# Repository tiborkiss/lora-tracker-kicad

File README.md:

# Träckthäspäck — a kid-friendly Meshtastic LoRa tracker

KiCad design of a small LoRa tracker board, created as a Swiss
[Zukunftstag](https://www.nationalerzukunftstag.ch/) project: with a group of children
we build a working Meshtastic tracker that the kids can take home and use.

The tracker is deliberately powered by **three ordinary AA batteries** — no
Li-ion cell — so it is simple and safe for children to handle and charge.

## Board

- Seeed Wio WM1110 module (LR1110 packet/radio controller)
- BMI270 motion sensor (wake-on-movement)
- ST7789 display on a 4-pin connector
- Active GNSS antenna + SMA LoRa antenna
- USB-C, SWD debug header
- Battery holder for 3× AA

## Firmware

The corresponding firmware is a Meshtastic fork and can be built from

<https://github.com/tiborkiss/firmware.git>, branch `bringup/wio-st7789-lcd`.

## Repository contents

- `träckthäspäck.kicad_sch` / `.kicad_pcb` / `.kicad_pro` — schematic and PCB
- `träckthäspäck.csv` — bill of materials
- `träcker 01.pdf` — board rendering
- `KiCAD-Shortcuts-PDF.pdf` — KiCad shortcut cheat sheet

## License

MIT — see [LICENSE](LICENSE).

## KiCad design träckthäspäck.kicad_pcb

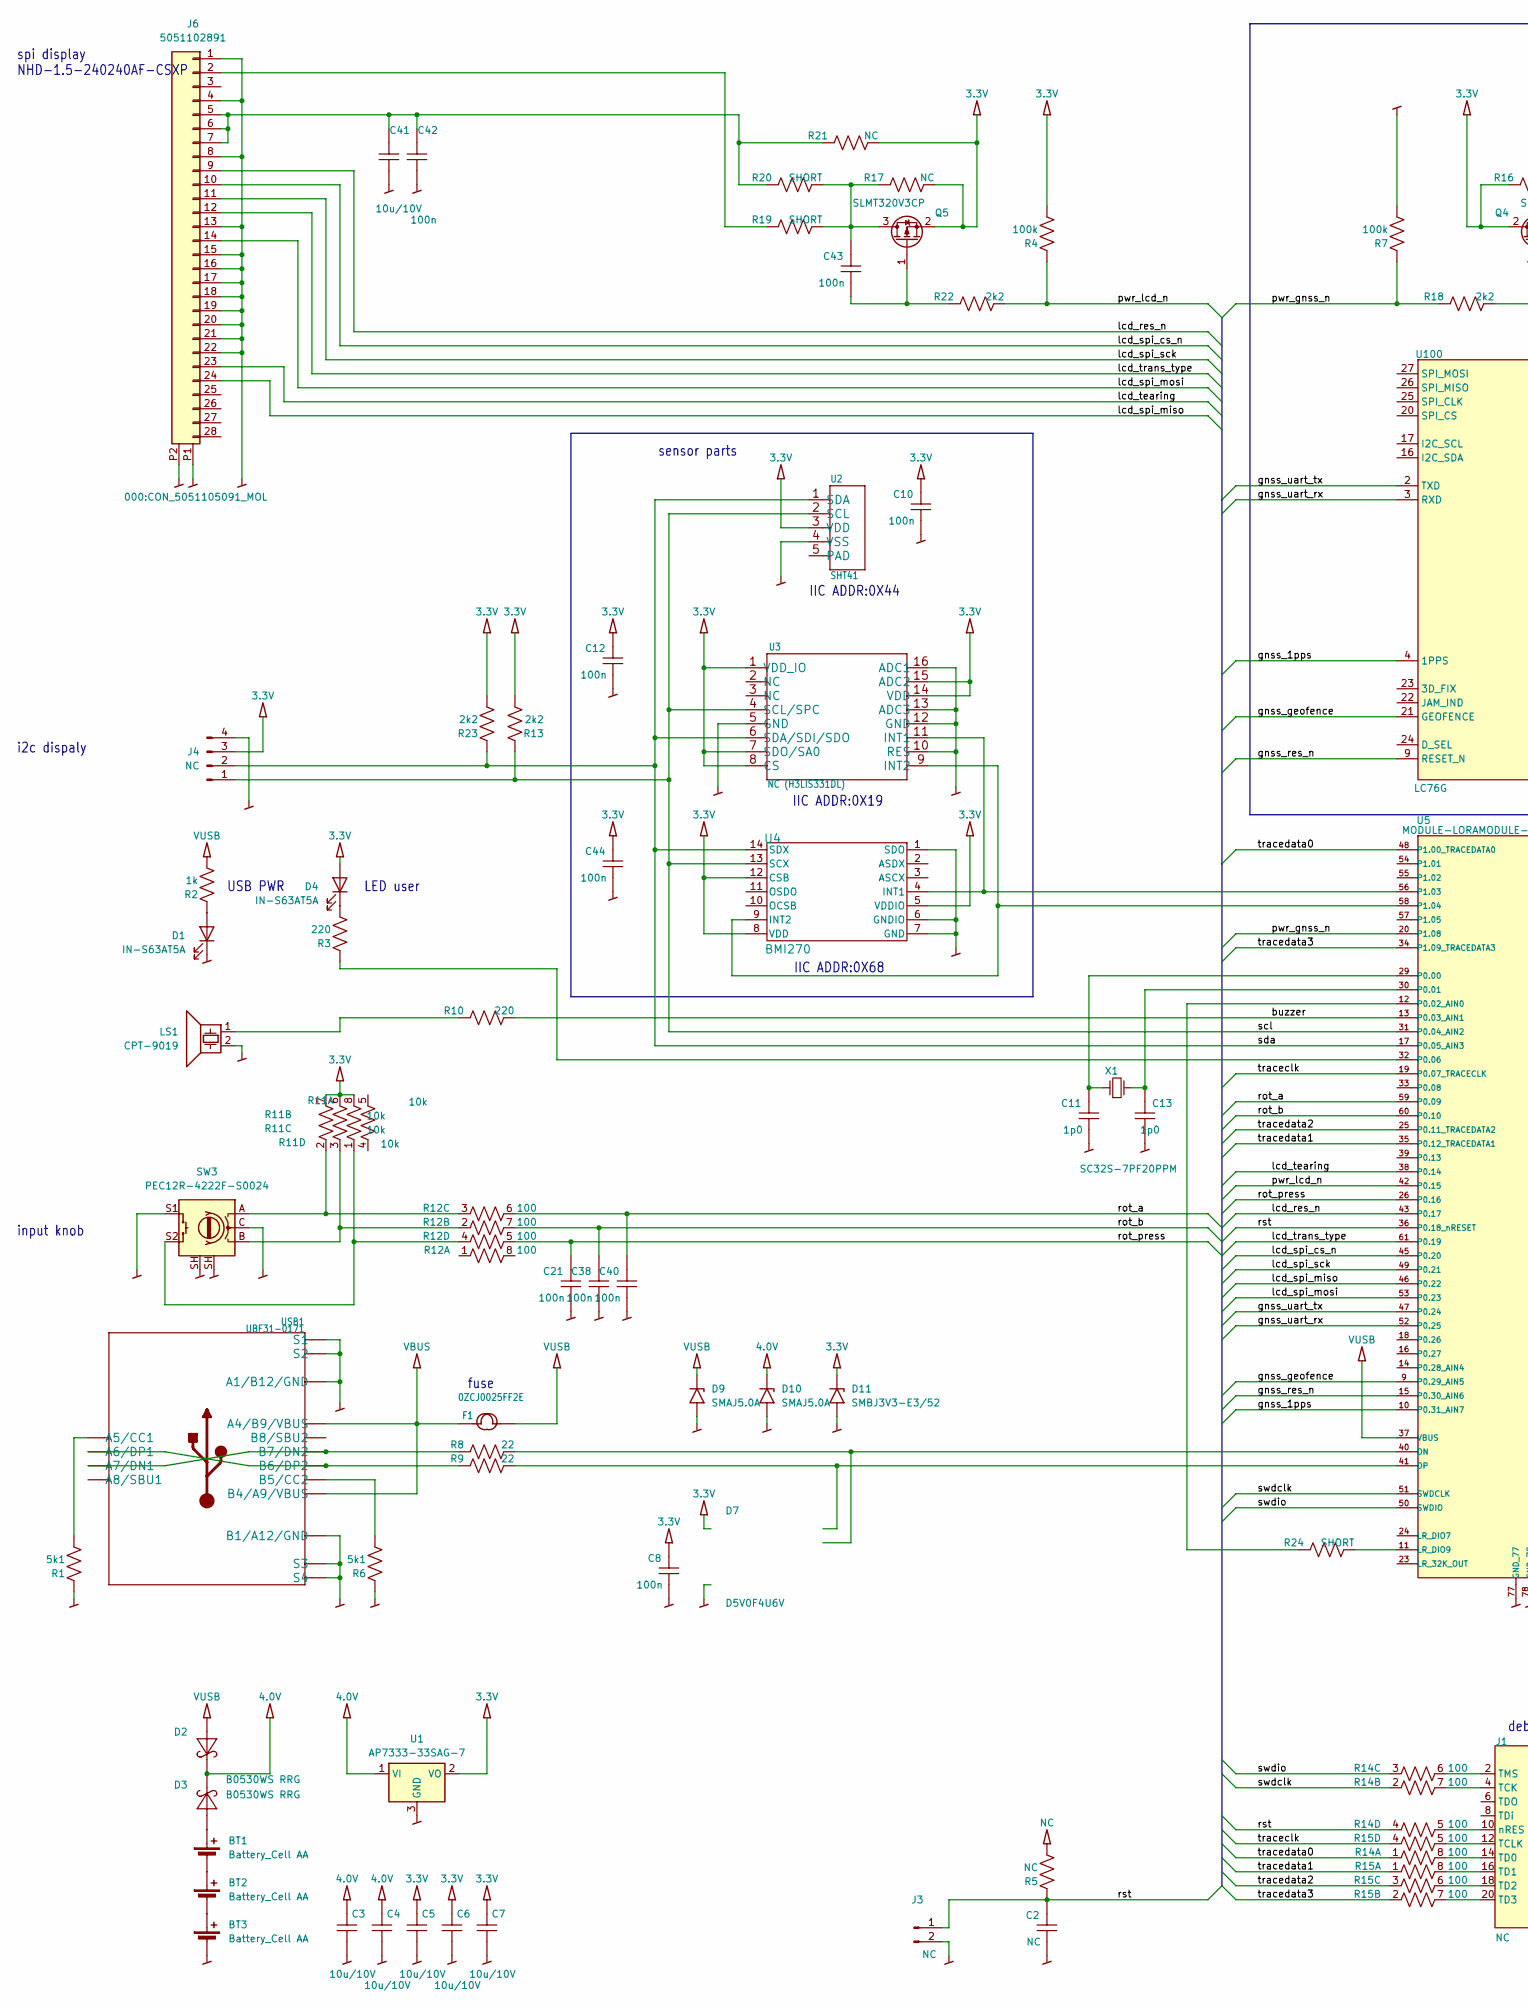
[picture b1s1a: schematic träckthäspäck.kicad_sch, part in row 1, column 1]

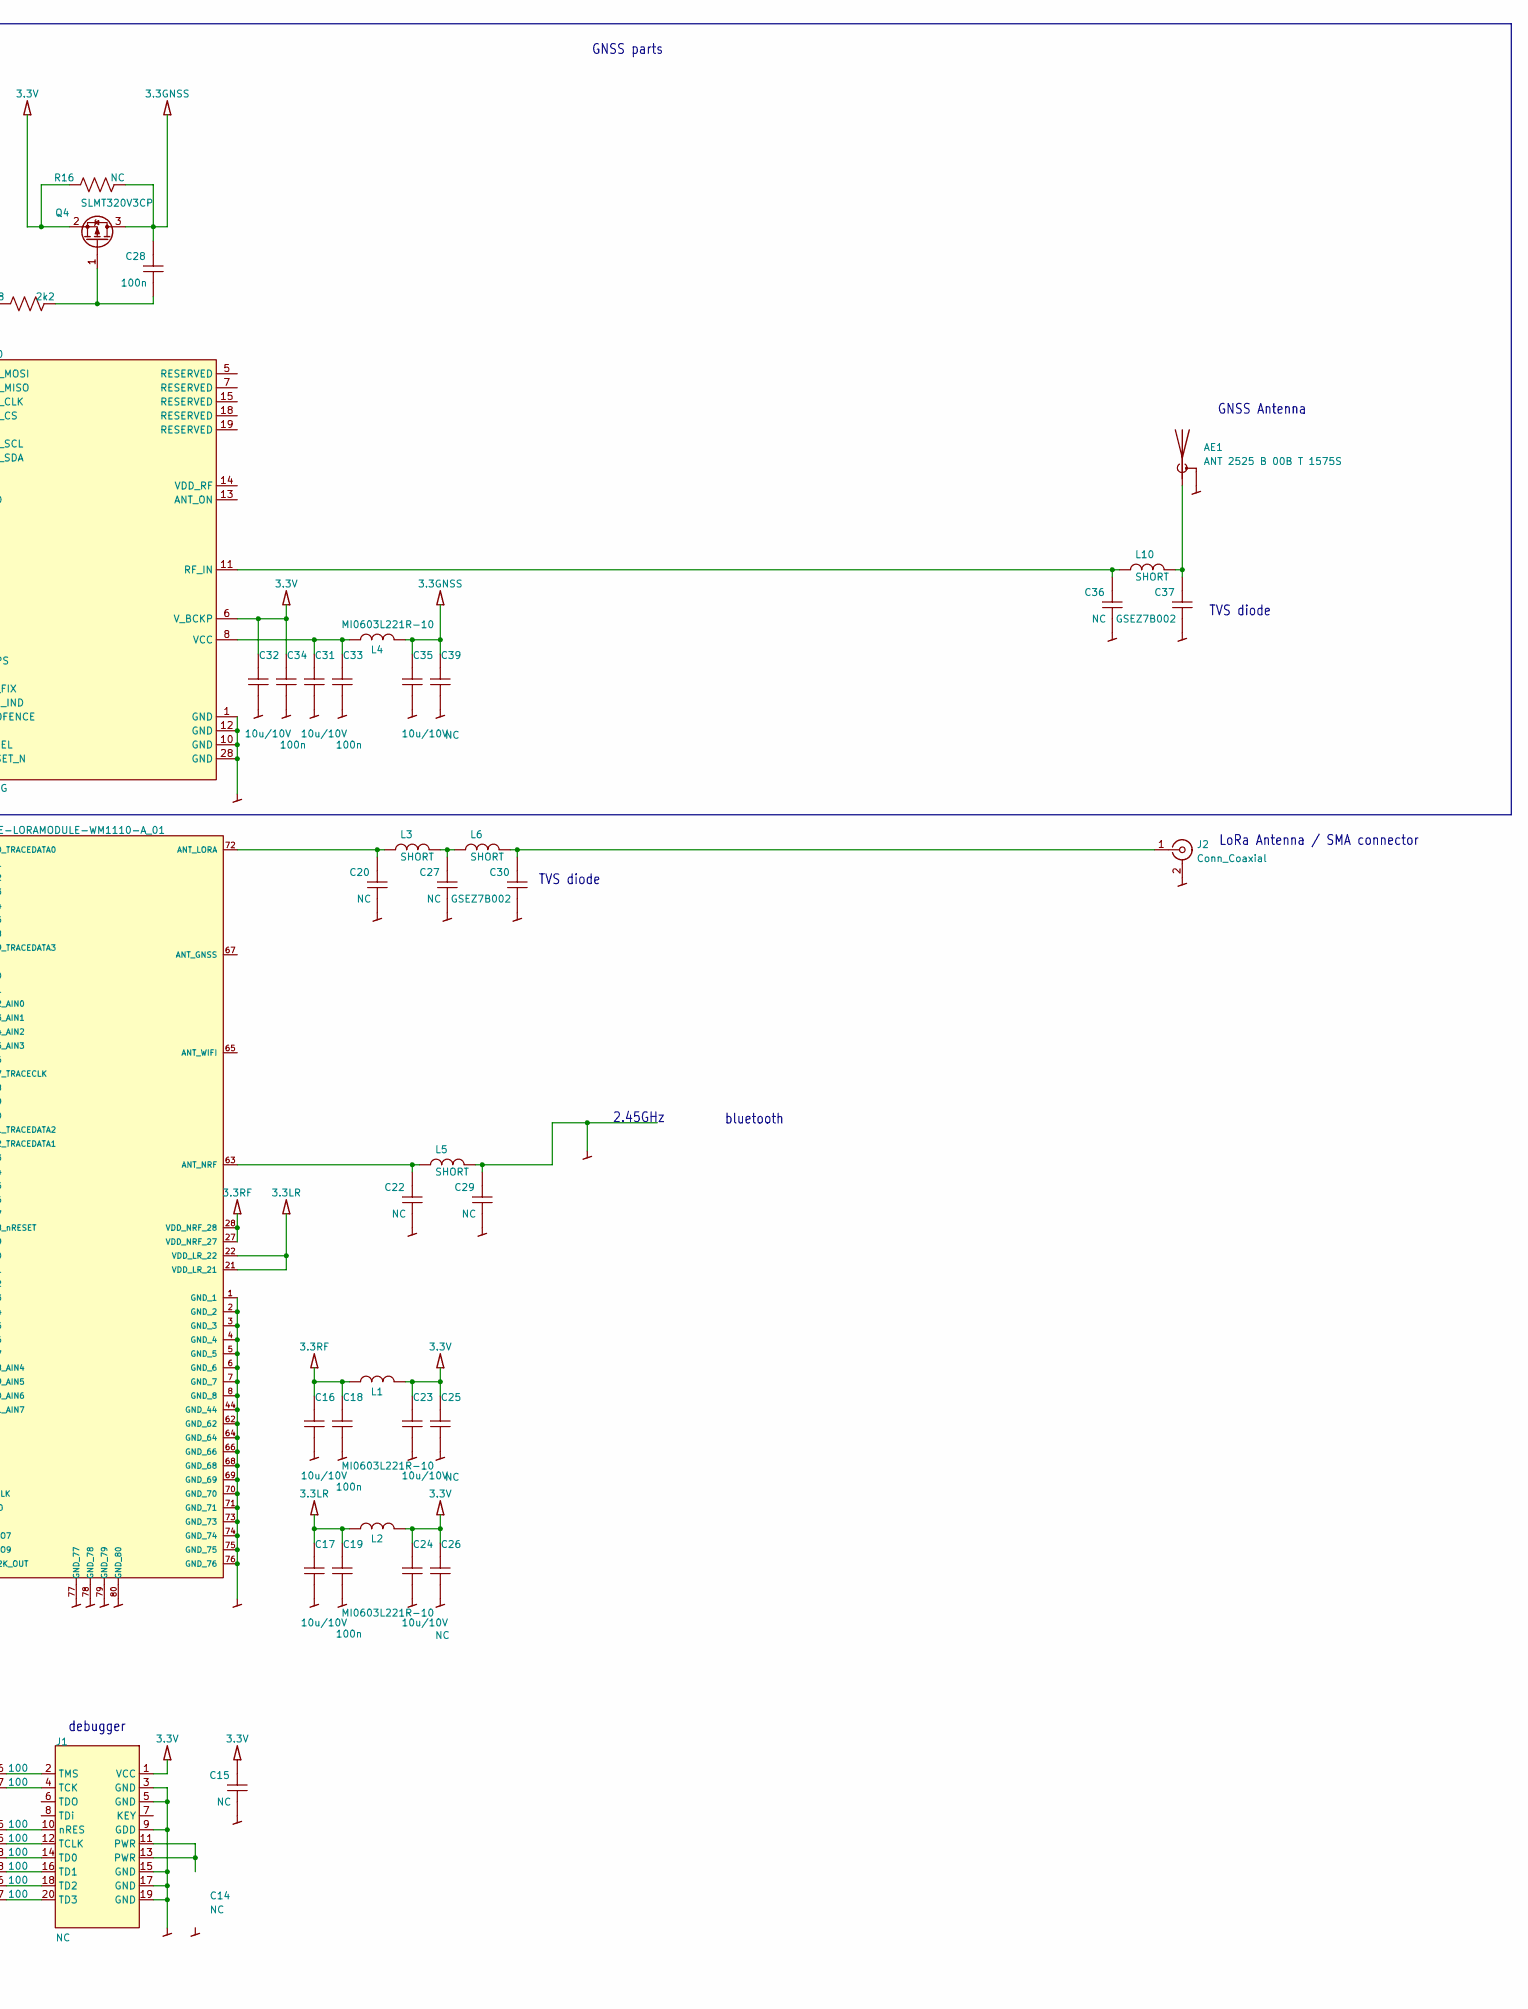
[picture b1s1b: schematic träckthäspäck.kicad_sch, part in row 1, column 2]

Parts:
AE1: ANT 2525 B 00B T 1575S
BT1, BT2, BT3: Battery_Cell AA; keystone_2460
C2, C14, C15, C20, C22, C25, C26, C27, C29, C36, C39: NC; 0402_C
C3, C4, C5, C6, C7, C16, C17, C23, C24, C31, C32, C35, C41: 10u/10V; 0603_C
C8, C10, C12, C18, C19, C21, C28, C33, C34, C38, C40, C42, C43, C44: 100n; 0402_C
C11, C13: 1p0; 0402_C
C30, C37: GSEZ7B002; 0402_C
D1, D4: IN-S63AT5A; LED_0603_1608Metric
D2, D3: B0530WS RRG; D_SOD-323F
D7: D5V0F4U6V; SOT-563
D9, D10: SMAJ5.0A; D_SMA
D11: SMBJ3V3-E3/52; D_SMA
F1: 0ZCJ0025FF2E; FS1206
J1: NC; PinHeader_2x10_P1.27mm_Vertical_SMD
J2: Conn_Coaxial; SMA_Amphenol_132134_Vertical
J3: NC; PinHeader_1x02_P2.00mm_Vertical
J4: NC; Molex_Micro-Latch_53253-0470_1x04_P2.00mm_Vertical
J6: 5051102891; CON_5051105091_MOL
L1, L2, L4: MI0603L221R-10; 0603_L
L3, L5, L6, L10: SHORT; 0402_L
LS1: CPT-9019; Buzzer_CUI_CPT-9019S-SMT
Q4, Q5: SLMT320V3CP; SOT-23
R1, R6: 5k1; 0402_R
R2: 1k; 0402_R
R3, R10: 220; 0402_R
R4, R7: 100k; 0402_R
R5, R16, R17, R21: NC; 0402_R
R8, R9: 22; 0402_R
R11: 10k; 0804-8
R12, R14, R15: 100; 0804-8
R13, R18, R22, R23: 2k2; 0402_R
R19, R20, R24: SHORT; 0402_R
SW3: PEC12R-4222F-S0024; RotaryEncoder_Bourns_Vertical_PEC12R-3x17F-S--oli
U1: AP7333-33SAG-7; SOT-23
U2: SHT41; SNR4-0.8-1.5X1.5X0.54MM
U3: NC (H3LIS331DL); LGA16-0.5-3X3MM
U4: BMI270; BMI270_BOS
U5: MODULE-LORAMODULE-WM1110-A_01; MODULE72_0D9_20X20X2MM
U100: LC76G
USB1: UBF31-0171; USB2.0-TYPE-C
X1: SC32S-7PF20PPM; XTAL2-1.5X3.2

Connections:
3.3GNSS: C28.1, C35.1, C39.1, L4.1, Q4.3 (D), R16.1
3.3LR: C17.1, C19.1, L2.2, U5.21 (VDD_LR_21), U5.22 (VDD_LR_22)
3.3RF: C16.1, C18.1, L1.2, U5.27 (VDD_NRF_27), U5.28 (VDD_NRF_28)
3.3V: C5.1, C6.1, C7.1, C8.1, C10.1, C12.1, C15.1, C23.1, C24.1, C25.1, C26.1, C32.1, C34.1, C44.1, D4.2 (A), D7.5 (VCC), D11.1 (A1), J1.1 (VCC), J4.3, L1.1, L2.1, Q4.2 (S), Q5.2 (S), R4.1, R11.6 (2), R11.7 (2), R11.8 (2), R13.1, R16.2, R17.1, R21.1, R23.1, U1.2 (VO), U2.3 (VDD), U3.1 (VDD_IO), U3.7 (SDO/SA0), U3.8 (CS), U3.14 (VDD), U3.15 (ADC2), U4.5 (VDDIO), U4.8 (VDD), U4.12 (CSB), U100.6 (V_BCKP)
4.0V: C3.1, C4.1, D2.1, D3.1, D10.1 (A1), U1.1 (VI)
/buzzer: R10.1, U5.13 (P0.03_AIN1)
/gnss_1pps: U5.10 (P0.31_AIN7), U100.4 (1PPS)
/gnss_geofence: U5.9 (P0.29_AIN5), U100.21 (GEOFENCE)
/gnss_res_n: U5.15 (P0.30_AIN6), U100.9 (RESET_N)
/gnss_uart_rx: U5.52 (P0.25), U100.3 (RXD)
/gnss_uart_tx: U5.47 (P0.24), U100.2 (TXD)
/lcd_res_n: J6.9, U5.43 (P0.17)
/lcd_spi_cs_n: J6.10, U5.45 (P0.20)
/lcd_spi_miso: J6.24, U5.46 (P0.22)
/lcd_spi_mosi: J6.14, U5.53 (P0.23)
/lcd_spi_sck: J6.11, U5.49 (P0.21)
/lcd_tearing: J6.23, U5.38 (P0.14)
/lcd_trans_type: J6.12, U5.61 (P0.19)
/pwr_gnss_n: R7.2, R18.2, U5.20 (P1.08)
/pwr_lcd_n: R4.2, R22.1, U5.42 (P0.15)
/rot_a: C40.1, R12.6 (2), U5.59 (P0.09)
/rot_b: C38.1, R12.7 (2), U5.60 (P0.10)
/rot_press: C21.1, R12.5 (2), U5.26 (P0.16)
/rst: C2.1, J3.1, R5.2, R14.4 (1), U5.36 (P0.18_nRESET)
/scl: J4.1, R13.2, U2.2 (SCL), U3.4 (SCL/SPC), U4.13 (SCX), U5.31 (P0.04_AIN2)
/sda: J4.2, R23.2, U2.1 (SDA), U3.6 (SDA/SDI/SDO), U4.14 (SDX), U5.17 (P0.05_AIN3)
/swdclk: R14.2 (1), U5.51 (SWDCLK)
/swdio: R14.3 (1), U5.50 (SWDIO)
/traceclk: R15.4 (1), U5.19 (P0.07_TRACECLK)
/tracedata0: R14.1, U5.48 (P1.00_TRACEDATA0)
/tracedata1: R15.1, U5.35 (P0.12_TRACEDATA1)
/tracedata2: R15.3 (1), U5.25 (P0.11_TRACEDATA2)
/tracedata3: R15.2 (1), U5.34 (P1.09_TRACEDATA3)
GND: AE1.2 (Shield), BT3.2 (-), C2.2, C3.2, C4.2, C5.2, C6.2, C7.2, C8.2, C10.2, C11.2, C12.2, C13.2, C14.2, C15.2, C16.2, C17.2, C18.2, C19.2, C20.2, C21.2, C22.2, C23.2, C24.2, C25.2, C26.2, C27.2, C29.2, C30.2, C31.2, C32.2, C33.2, C34.2, C35.2, C36.2, C37.2, C38.2, C39.2, C40.2, C41.2, C42.2, C44.2, D1.1 (K), D7.2 (GND), D9.2 (A2), D10.2 (A2), D11.2 (A2), J1.3 (GND), J1.5 (GND), J1.9 (GDD), J1.15 (GND), J1.17 (GND), J1.19 (GND), J2.2 (Ext), J3.2, J4.4, J6.1, J6.4, J6.8, J6.13, J6.15, J6.16, J6.17, J6.18, J6.19, J6.20, J6.21, J6.22, J6.P1, J6.P2, LS1.2, R1.2, R6.2, R7.1, SW3.C, SW3.S1, SW3.SH, U1.3 (GND), U2.4 (VSS), U3.5 (GND), U3.10 (RES), U3.12 (GND), U3.13 (ADC3), U3.16 (ADC1), U4.1 (SDO), U4.6 (GNDIO), U4.7 (GND), U5.1 (GND_1), U5.2 (GND_2), U5.3 (GND_3), U5.4 (GND_4), U5.5 (GND_5), U5.6 (GND_6), U5.7 (GND_7), U5.8 (GND_8), U5.44 (GND_44), U5.62 (GND_62), U5.64 (GND_64), U5.66 (GND_66), U5.68 (GND_68), U5.69 (GND_69), U5.70 (GND_70), U5.71 (GND_71), U5.73 (GND_73), U5.74 (GND_74), U5.75 (GND_75), U5.76 (GND_76), U5.77 (GND_77), U5.78 (GND_78), U5.79 (GND_79), U5.80 (GND_80), U100.1 (GND), U100.10 (GND), U100.12 (GND), U100.28 (GND), USB1.A1_B12 (A1/B12/GND), USB1.B1_A12 (B1/A12/GND), USB1.S1, USB1.S2, USB1.S3, USB1.S4, USB1.S5 (S1), USB1.S6 (S2)
GND_A2: C29.1, L5.1
NC: R5.1
unnamed: AE1.1 (A), C37.1, L10.1
unnamed: BT1.1 (+), D3.2
unnamed: BT1.2 (-), BT2.1 (+)
unnamed: BT2.2 (-), BT3.1 (+)
unnamed: C14.1, J1.11 (PWR), J1.13 (PWR)
unnamed: C27.1, L3.1, L6.2
unnamed: D1.2 (A), R2.2
unnamed: D4.1 (K), R3.1
unnamed: D7.1 (CH1), R9.1, U5.41 (DP)
unnamed: D7.3 (CH2), R8.1, U5.40 (DN)
unnamed: J1.4 (TCK), R14.7 (2)
unnamed: J1.12 (TCLK), R15.5 (2)
unnamed: J1.14 (TD0), R14.8 (2)
unnamed: J1.16 (TD1), R15.8 (2)
unnamed: J1.18 (TD2), R15.6 (2)
unnamed: J1.20 (TD3), R15.7 (2)
unnamed: J1.2 (TMS), R14.6 (2)
unnamed: J1.10 (nRES), R14.5 (2)
unnamed: C30.1, J2.1 (In), L6.1
unnamed: J6.2, R19.2
unnamed: C41.1, C42.1, J6.5, J6.6, J6.7, R20.2, R21.2
unnamed: LS1.1, R10.2
unnamed: C28.2, Q4.1 (G), R18.1
unnamed: C43.1, Q5.3 (D), R17.2, R19.1, R20.1
unnamed: C43.2, Q5.1 (G), R22.2
unnamed: R11.2 (1), R12.3 (1), SW3.A
unnamed: R11.3 (1), R12.2 (1), SW3.B
unnamed: R11.1, R12.4 (1), SW3.S2
unnamed: U3.11 (INT1), U4.4 (INT1), U5.56 (P1.03)
unnamed: U3.9 (INT2), U4.9 (INT2), U5.58 (P1.04)
unnamed: C20.1, L3.2, U5.72 (ANT_LORA)
unnamed: C22.1, L5.2, U5.63 (ANT_NRF)
unnamed: R24.1, U5.11 (LR_DIO9)
unnamed: C11.1, U5.29 (P0.00), X1.2
unnamed: C13.1, U5.30 (P0.01), X1.1
unnamed: R24.2, U5.12 (P0.02_AIN0)
unnamed: R3.2, U5.32 (P0.06)
unnamed: C36.1, L10.2, U100.11 (RF_IN)
unnamed: C31.1, C33.1, L4.2, U100.8 (VCC)
unnamed: R1.1, USB1.A5 (A5/CC1)
unnamed: R9.2, USB1.A6 (A6/DP1), USB1.B6 (B6/DP2)
unnamed: R8.2, USB1.A7 (A7/DN1), USB1.B7 (B7/DN2)
unnamed: R6.1, USB1.B5 (B5/CC2)
VBUS: F1.1, USB1.A4_B9 (A4/B9/VBUS), USB1.B4_A9 (B4/A9/VBUS)
VUSB: D2.2, D9.1 (A1), F1.2, R2.1, U5.37 (VBUS)

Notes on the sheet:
sensor parts
2.45GHz
TVS diode
GNSS Antenna
fuse
spi display NHD-1.5-240240AF-CSXP
LED user
IIC ADDR:0X44
IIC ADDR:0X68
USB PWR
bluetooth
IIC ADDR:0X19
LoRa Antenna / SMA connector
i2c dispaly
input knob
debugger
GNSS parts

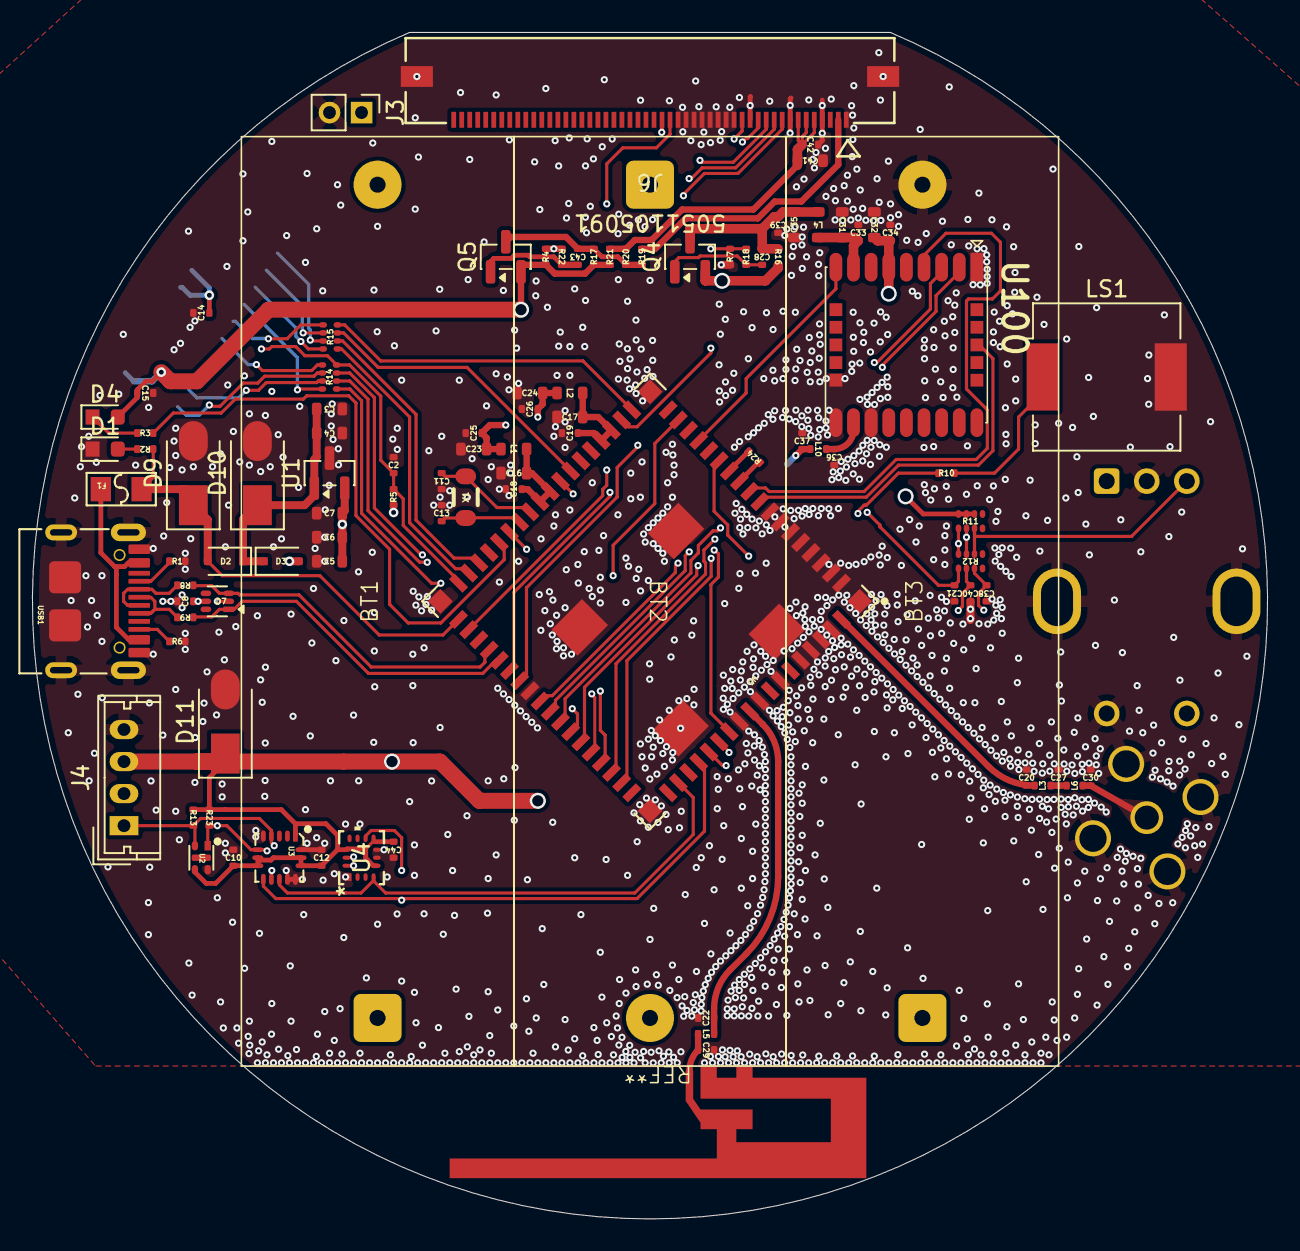
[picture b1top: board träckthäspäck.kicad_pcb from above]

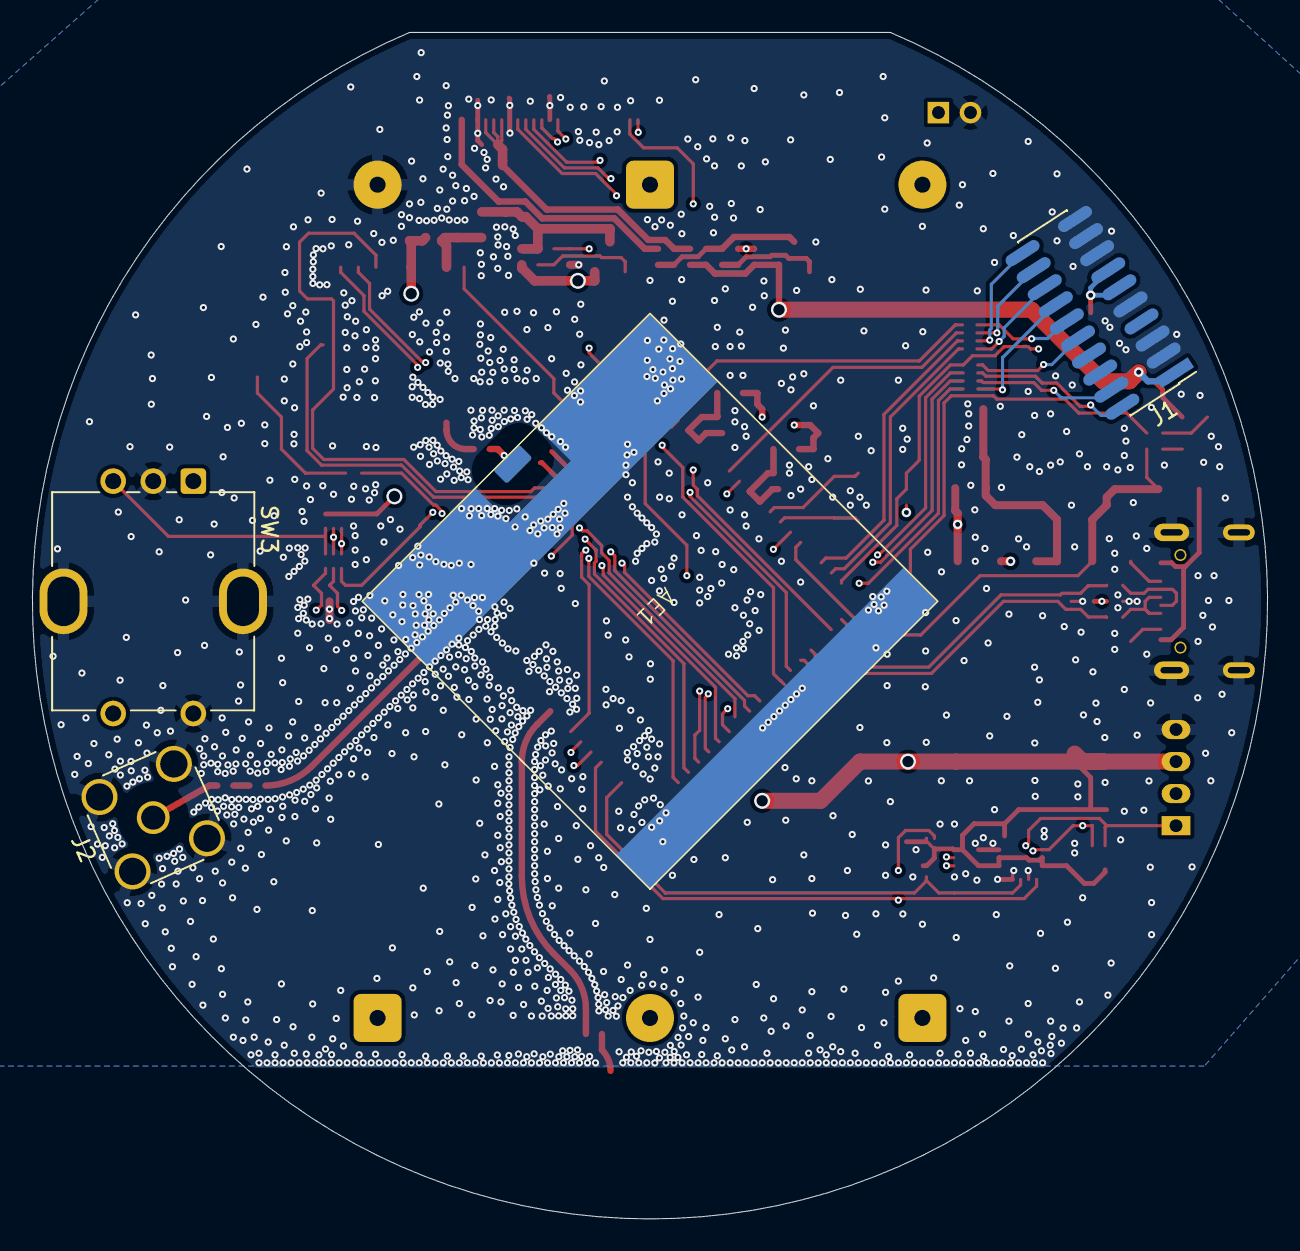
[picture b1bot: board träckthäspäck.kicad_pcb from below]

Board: 4 copper layers, 77.1 x 74.0 mm, 103 parts (4 on the bottom side), 80 nets.
